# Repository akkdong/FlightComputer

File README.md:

# Flight Computer(Assistant)

## Hardware 
* Raspberry PI Zero
* E-Ink
* STM32H7 Dual core
* Peripherals
  * 10DOF IMU
  * GPS
  * SD-Card
  * Battery change
  * Codec
  * ...
  <p>

  <p>
* ...

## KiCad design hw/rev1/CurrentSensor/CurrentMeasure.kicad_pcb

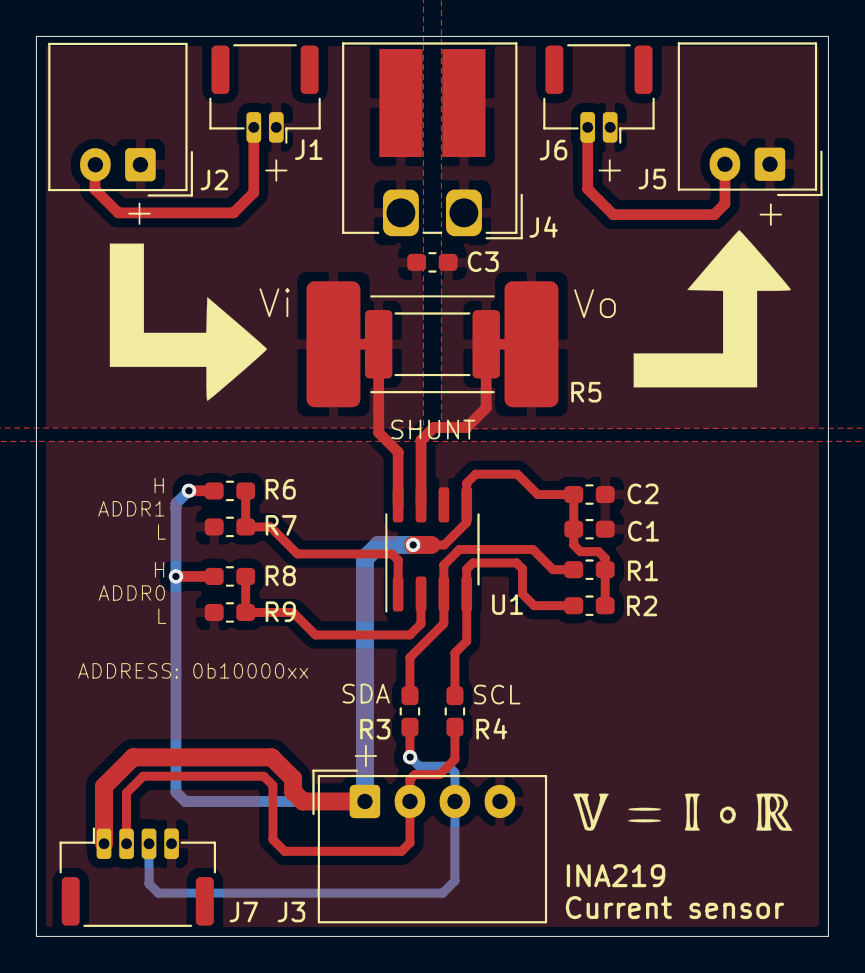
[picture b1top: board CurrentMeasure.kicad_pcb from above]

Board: 2 copper layers, 44.0 x 50.0 mm, 21 parts (0 on the bottom side), 10 nets.

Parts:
C1, C3: 0.1uF; C_0603_1608Metric_Pad1.05x0.95mm_HandSolder
C2: 10Uf; C_0603_1608Metric_Pad1.05x0.95mm_HandSolder
J1, J6: Conn_01x02; Molex_CLIK-Mate_502386-0270_1x02-1MP_P1.25mm_Horizontal
J2, J5: Conn_01x02; Molex_SPOX_5268-02A_1x02_P2.50mm_Horizontal
J3: Conn_01x04; Molex_SPOX_5268-04A_1x04_P2.50mm_Horizontal
J4: Conn_01x02; Wago_734-162_1x02_P3.50mm_Horizontal
J7: Conn_01x04; Molex_CLIK-Mate_502386-0470_1x04-1MP_P1.25mm_Horizontal
R1, R2: 10K; R_0603_1608Metric_Pad1.05x0.95mm_HandSolder
R3, R4: 33R; R_0603_1608Metric_Pad1.05x0.95mm_HandSolder
R5: 2mR; R_2512_6332Metric_Pad1.52x3.35mm_HandSolder
R6, R7, R8, R9: 100R; R_0603_1608Metric_Pad1.05x0.95mm_HandSolder
R10: N/C; R_4527
U1: INA219AxD; SOIC-8_3.9x4.9mm_P1.27mm

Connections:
/VIN: C3.1, J1.1, J2.1, J4.2, R5.1, R10.1, U1.8
/VOUT: C3.2, J4.1, J5.1, J6.1, R5.2, R10.2, U1.7
GND: C1.2, C2.2, J1.2, J2.2, J3.4, J5.2, J6.2, J7.4, R7.2, R9.2, U1.6
unnamed: J3.2, J7.2, R4.1
unnamed: J3.3, J7.3, R3.1
unnamed: R1.2, R3.2, U1.3
unnamed: R2.2, R4.2, U1.4
unnamed: R6.1, R7.1, U1.1
unnamed: R8.1, R9.1, U1.2
VCC: C1.1, C2.1, J3.1, J7.1, R1.1, R2.1, R6.2, R8.2, U1.5

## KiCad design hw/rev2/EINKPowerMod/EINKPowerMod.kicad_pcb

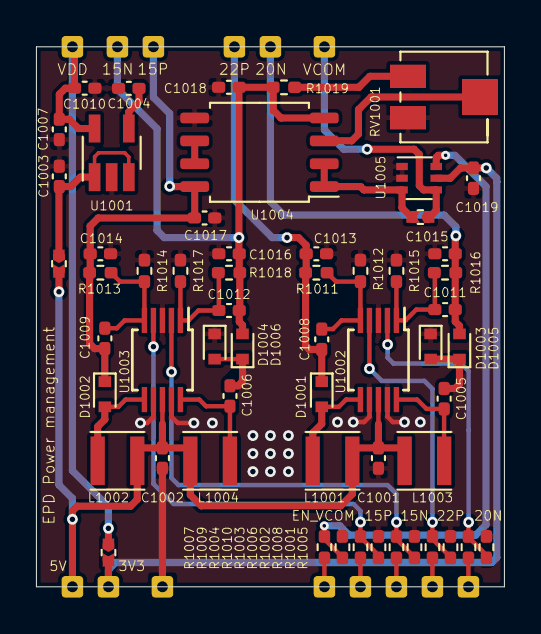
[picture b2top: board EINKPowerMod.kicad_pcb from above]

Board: 2 copper layers, 26.0 x 30.0 mm, 71 parts (0 on the bottom side), 35 nets.

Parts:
C1001, C1002: 4.7uF; C_0402_1005Metric_Pad0.74x0.62mm_HandSolder
C1003, C1004, C1013, C1014, C1015, C1016: 1uF; C_0402_1005Metric_Pad0.74x0.62mm_HandSolder
C1005, C1006, C1007, C1017, C1018, C1019: 0.1uF; C_0402_1005Metric_Pad0.74x0.62mm_HandSolder
C1008, C1009: 4.7pF; C_0402_1005Metric_Pad0.74x0.62mm_HandSolder
C1010: 10uF; C_0402_1005Metric_Pad0.74x0.62mm_HandSolder
C1011, C1012: 100pF; C_0402_1005Metric_Pad0.74x0.62mm_HandSolder
D1001, D1002, D1003, D1004, D1005, D1006: 1N4001; D_SOD-523
J1001, J1002, J1003, J1004, J1005, J1006, J1007, J1008, J1009, J1010, J1011, J1012, J1013, J1014: Conn_01x01; PMIC_HOLE
JP1001: Close; Jumper_0402_1005Metric
JP1002, JP1003: Open; Jumper_0402_1005Metric
L1001, L1002, L1003, L1004: 22uH; L_Taiyo-Yuden_MD-3030
R1001, R1002, R1003, R1004, R1007: 33R; R_0402_1005Metric_Pad0.72x0.64mm_HandSolder
R1005, R1006, R1008, R1009, R1010: 100K; R_0402_1005Metric_Pad0.72x0.64mm_HandSolder
R1011: 2M; R_0402_1005Metric_Pad0.72x0.64mm_HandSolder
R1012: 120K; R_0402_1005Metric_Pad0.72x0.64mm_HandSolder
R1013: 300K; R_0402_1005Metric_Pad0.72x0.64mm_HandSolder
R1014: 27K; R_0402_1005Metric_Pad0.72x0.64mm_HandSolder
R1015: 39K; R_0402_1005Metric_Pad0.72x0.64mm_HandSolder
R1016: 560K; R_0402_1005Metric_Pad0.72x0.64mm_HandSolder
R1017: 10K; R_0402_1005Metric_Pad0.72x0.64mm_HandSolder
R1018: 110K; R_0402_1005Metric_Pad0.72x0.64mm_HandSolder
R1019: 200K; R_0402_1005Metric_Pad0.72x0.64mm_HandSolder
RV1001: 100K; Potentiometer_Bourns_3214J_Horizontal
U1001: XC6220B331MR-G; SOT-23-5_HandSoldering
U1002, U1003: LT1945; MSOP-10_3x3mm_P0.5mm
U1004: LM358; SOIC-8_5.275x5.275mm_P1.27mm
U1005: NC7SB3157P6X; SOT-363_SC-70-6

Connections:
+15V: C1009.1, C1014.1, C1017.1, D1002.1, J1012.1, R1013.2, U1004.8
+22V: C1008.1, C1013.1, D1001.1, J1009.1, R1011.2
-15V: C1012.2, C1016.1, C1018.2, D1006.2, J1013.1, R1018.2, R1019.2, U1004.4
-20V: C1011.2, C1015.1, D1005.2, J1010.1, R1016.2
/EN_15N: J1005.1, R1003.2
/EN_15P: J1004.1, R1004.2
/EN_20N: J1007.1, R1001.2
/EN_22P: J1006.1, R1002.2
/EN_VCOM: J1008.1, R1007.1
GND: C1001.2, C1002.2, C1003.1, C1004.1, C1007.1, C1010.2, C1013.2, C1014.2, C1015.2, C1016.2, C1017.2, C1018.1, C1019.1, D1003.1, D1004.1, J1003.1, R1005.2, R1006.2, R1008.2, R1009.2, R1010.2, R1012.2, R1014.2, R1015.2, R1017.2, RV1001.1, U1001.2, U1002.3, U1002.7, U1002.9, U1003.3, U1003.7, U1003.9, U1004.5, U1005.1, U1005.2
unnamed: C1003.2, JP1001.2, U1001.1, U1001.3
unnamed: C1004.2, U1001.4
unnamed: C1005.1, D1003.2, D1005.1
unnamed: C1005.2, L1003.1, U1002.10
unnamed: C1006.1, D1004.2, D1006.1
unnamed: C1006.2, L1004.1, U1003.10
unnamed: C1008.2, R1011.1, R1012.1, U1002.5
unnamed: C1009.2, R1013.1, R1014.1, U1003.5
unnamed: C1011.1, R1015.1, R1016.1, U1002.1
unnamed: C1012.1, R1017.1, R1018.1, U1003.1
unnamed: D1001.2, L1001.2, U1002.6
unnamed: D1002.2, L1002.2, U1003.6
unnamed: JP1003.1, U1004.1, U1004.2, U1005.3
unnamed: R1001.1, R1005.1, U1002.2
unnamed: R1002.1, R1008.1, U1002.4
unnamed: R1003.1, R1006.1, U1003.2
unnamed: R1004.1, R1010.1, U1003.4
unnamed: R1007.2, R1009.1, U1005.6
unnamed: R1019.1, RV1001.3
unnamed: RV1001.2, U1004.3
unnamed: U1004.6, U1004.7
VCC_3V3: C1019.2, J1002.1, JP1002.1, U1005.5
VCC_5V: C1001.1, C1002.1, J1001.1, JP1001.1, L1001.1, L1002.1, L1003.2, L1004.2, U1002.8, U1003.8
VCC_EINK: C1007.2, C1010.1, J1014.1, JP1002.2, U1001.5
VCOM: J1011.1, JP1003.2, U1005.4

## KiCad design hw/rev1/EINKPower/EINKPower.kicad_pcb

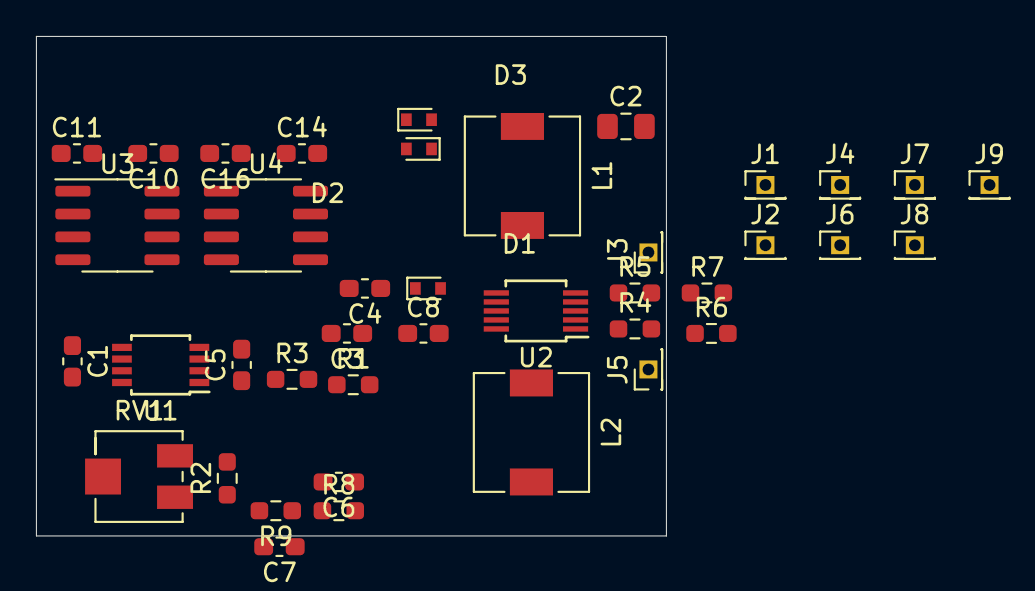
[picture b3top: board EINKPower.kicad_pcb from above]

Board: 2 copper layers, 35.0 x 27.8 mm, 40 parts (0 on the bottom side), 18 nets, no tracks yet.

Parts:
C1, C5, C8: 0.1uF; C_0603_1608Metric_Pad1.05x0.95mm_HandSolder
C2: 4.7uF; C_0805_2012Metric_Pad1.15x1.40mm_HandSolder
C3: 4.7pF; C_0603_1608Metric_Pad1.05x0.95mm_HandSolder
C4, C6, C11, C16: 1uF; C_0603_1608Metric_Pad1.05x0.95mm_HandSolder
C7: 100pF; C_0603_1608Metric_Pad1.05x0.95mm_HandSolder
C10, C14: 4.7uF; C_0603_1608Metric_Pad1.05x0.95mm_HandSolder
D1, D2, D3: 1N4001; D_SOD-523
J1, J2, J3, J4, J5, J6, J7, J8, J9: Conn_01x01; PinHeader_1x01_P1.27mm_Vertical
L1, L2: 22uH; L_6.3x6.3_H3
R1: 2M; R_0603_1608Metric_Pad0.98x0.95mm_HandSolder
R2: 200K; R_0603_1608Metric_Pad0.98x0.95mm_HandSolder
R3: 120K; R_0603_1608Metric_Pad0.98x0.95mm_HandSolder
R4, R5: 33R; R_0603_1608Metric_Pad0.98x0.95mm_HandSolder
R6, R7: 100K; R_0603_1608Metric_Pad0.98x0.95mm_HandSolder
R8: 39K; R_0603_1608Metric_Pad0.98x0.95mm_HandSolder
R9: 560K; R_0603_1608Metric_Pad0.98x0.95mm_HandSolder
RV1: 100K; Potentiometer_Bourns_3214J_Horizontal
U1: LM358; TSSOP-8_3x3mm_P0.65mm
U2: LT1945; MSOP-10_3x3mm_P0.5mm
U3: MC78L15_SO8; SOIC-8_3.9x4.9mm_P1.27mm
U4: MC79L15_SO8; SOIC-8_3.9x4.9mm_P1.27mm

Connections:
+15V: C1.1, C11.1, J8.1, U1.8, U3.1
+22V: C3.1, C4.1, C10.1, D1.1, J1.1, R1.2, U3.8
-15V: C5.2, C16.2, J9.1, R2.2, U1.4, U4.1
-20V: C6.1, C7.2, C14.2, D3.2, J4.1, R9.2, U4.2, U4.3, U4.6, U4.7
/EN_VDD: J3.1, R5.2
/EN_VEE: J5.1, R4.2
GND: C1.2, C2.2, C4.2, C5.1, C6.2, C10.2, C11.2, C14.1, C16.1, D2.1, J6.1, R3.2, R6.2, R7.2, R8.2, RV1.1, U2.3, U2.7, U2.9, U3.2, U3.3, U3.6, U3.7, U4.5
unnamed: C3.2, R1.1, R3.1, U2.5
unnamed: C7.1, R8.1, R9.1, U2.1
unnamed: C8.1, D2.2, D3.1
unnamed: C8.2, L2.1, U2.10
unnamed: D1.2, L1.2, U2.6
unnamed: R2.1, RV1.3
unnamed: R4.1, R6.1, U2.2
unnamed: R5.1, R7.1, U2.4
unnamed: RV1.2, U1.3
VCC_5V: C2.1, J2.1, L1.1, L2.2, U2.8
VCOM: J7.1, U1.1, U1.2

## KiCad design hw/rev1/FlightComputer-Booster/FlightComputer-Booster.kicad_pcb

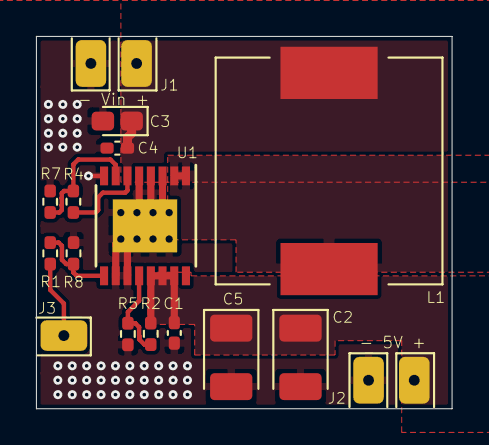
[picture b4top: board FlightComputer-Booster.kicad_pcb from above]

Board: 2 copper layers, 23.1 x 20.7 mm, 16 parts (0 on the bottom side), 8 nets.

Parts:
C1: 2.2uF; C_0402_1005Metric_Pad0.74x0.62mm_HandSolder
C2, C5: 100uF; CP_EIA-3528-15_AVX-H_Pad1.50x2.35mm_HandSolder
C3: 10uF; CP_EIA-1608-08_AVX-J_Pad1.25x1.05mm_HandSolder
C4: 0.1uF; C_0402_1005Metric_Pad0.74x0.62mm_HandSolder
J1, J2: Conn_01x02; PinHeader_1x02_P2.54mm_Vertical
J3: Conn_01x01; PinHeader_1x01_P2.54mm_Vertical
L1: 68uH w/2A; L_12x12mm_H6mm
R1: 33R; R_0402_1005Metric_Pad0.72x0.64mm_HandSolder
R2, R4: 1.87M; R_0402_1005Metric_Pad0.72x0.64mm_HandSolder
R5, R7: 340K; R_0402_1005Metric_Pad0.72x0.64mm_HandSolder
R8: 100K; R_0402_1005Metric_Pad0.72x0.64mm_HandSolder
U1: TPS61032PWR; TSSOP-16-1EP_4.4x5mm_P0.65mm

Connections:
/EN: R1.2, R8.1, U1.9
/FB: R2.2, R5.1, U1.12
/LBI: R4.2, R7.1, U1.7
/SW: L1.2, U1.1, U1.2
GND: C1.2, C2.2, C3.2, C4.2, C5.2, J1.2, J2.2, R5.2, R7.2, R8.2, U1.3, U1.4, U1.5, U1.8, U1.10, U1.11, U1.17
unnamed: J3.1, R1.1
VCC_5V: C1.1, C2.1, C5.1, J2.1, R2.1, U1.13, U1.14, U1.15
VCC_BAT: C3.1, C4.1, J1.1, L1.1, R4.1, U1.6

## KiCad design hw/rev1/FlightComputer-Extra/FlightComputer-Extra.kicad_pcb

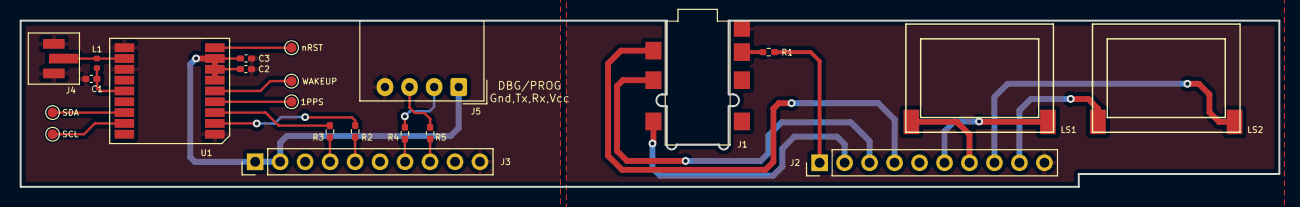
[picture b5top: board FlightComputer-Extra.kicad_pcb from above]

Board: 2 copper layers, 128.0 x 16.9 mm, 22 parts (0 on the bottom side), 27 nets.

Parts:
C1: 22pF; C_0402_1005Metric_Pad0.74x0.62mm_HandSolder
C2: 0.1uF; C_0402_1005Metric_Pad0.74x0.62mm_HandSolder
C3: 1uF; C_0402_1005Metric_Pad0.74x0.62mm_HandSolder
J1: SJ-43617-SMT
J2, J3: Conn_01x10; PinHeader_1x10_P2.54mm_Vertical
J4: IPEX_IPX; IPEX-IPX
J5: Conn_DEBUG; Molex_SPOX_5268-04A_1x04_P2.50mm_Horizontal
L1: 33nH; L_0402_1005Metric
LS1, LS2: Speaker; SM150808-8
R1: 100K; R_0402_1005Metric_Pad0.72x0.64mm_HandSolder
R2, R3, R4, R5: 33R; R_0402_1005Metric_Pad0.72x0.64mm_HandSolder
TP1: SCL; TestPoint_Pad_D1.0mm
TP2: SDA; TestPoint_Pad_D1.0mm
TP3: nRST; TestPoint_Pad_D1.0mm
TP4: WAKEUP; TestPoint_Pad_D1.0mm
TP5: 1PPS; TestPoint_Pad_D1.0mm
U1: Teseo-LIV3F

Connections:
/DEBUG_RX: J3.7, R4.2
/DEBUG_TX: J3.8, R5.2
/GPS_RX: J3.4, R3.1
/GPS_TX: J3.5, R2.1
/HP_DETECT: J1.4, J2.4
/HP_LEFT: J1.2, J2.2
/HP_RIGHT: J1.3, J2.3
/SPK_LN: J2.7, LS1.2
/SPK_LP: J2.6, LS1.1
/SPK_RN: J2.9, LS2.2
/SPK_RP: J2.8, LS2.1
GND: C1.1, C2.1, C3.1, J3.10, J4.2, J4.3, J5.4, U1.1, U1.10, U1.12
GNDA: J1.1, J2.10
unnamed: C1.2, L1.1, U1.14
unnamed: J1.12, R1.2
unnamed: J4.1, L1.2, U1.11
unnamed: J5.2, R4.1
unnamed: J5.3, R5.1
unnamed: R2.2, U1.2
unnamed: R3.2, U1.3
unnamed: TP1.1, U1.17
unnamed: TP2.1, U1.16
unnamed: TP3.1, U1.9
unnamed: TP4.1, U1.5
unnamed: TP5.1, U1.4
VCC_3V3: J2.1, R1.1
VCC_PERIH: C2.2, C3.2, J3.1, J3.2, J5.1, U1.6, U1.7, U1.8

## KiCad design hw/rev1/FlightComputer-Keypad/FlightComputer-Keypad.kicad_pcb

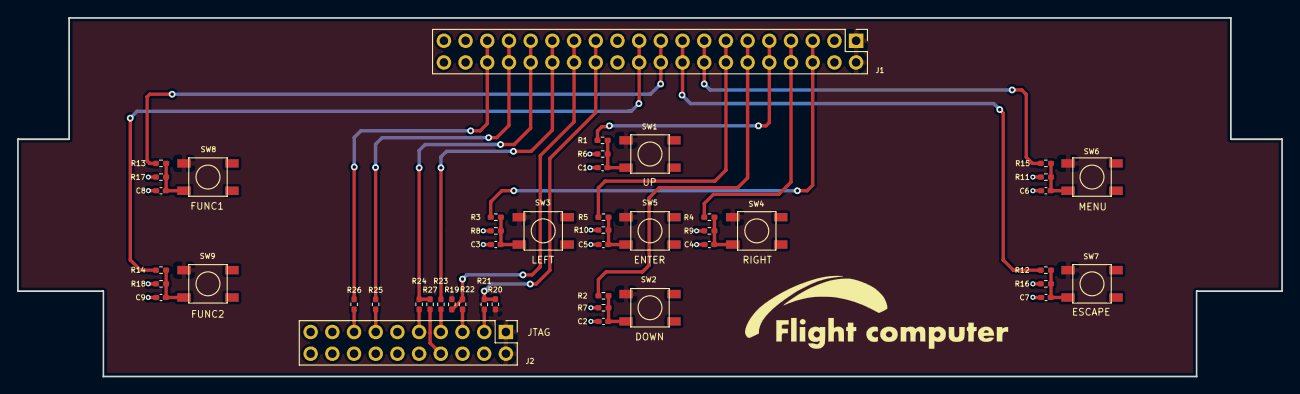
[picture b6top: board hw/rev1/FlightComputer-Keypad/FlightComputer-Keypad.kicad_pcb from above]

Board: 2 copper layers, 148.0 x 42.0 mm, 47 parts (0 on the bottom side), 32 nets.

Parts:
C1, C2, C3, C4, C5, C6, C7, C8, C9: 0.1uF; C_0402_1005Metric_Pad0.74x0.62mm_HandSolder
J1: Conn_02x20_Odd_Even; PinHeader_2x20_P2.54mm_Vertical
J2: Conn_02x10_Odd_Even; PinHeader_2x10_P2.54mm_Vertical
R1, R2, R3, R4, R5, R11, R12, R13, R14: 1K; R_0402_1005Metric_Pad0.72x0.64mm_HandSolder
R6, R7, R8, R9, R10, R15, R16, R17, R18, R19, R20, R27: 100K; R_0402_1005Metric_Pad0.72x0.64mm_HandSolder
R21, R22, R23, R24, R25, R26: 33R; R_0402_1005Metric_Pad0.72x0.64mm_HandSolder
SW1, SW2, SW3, SW4, SW5, SW6, SW7, SW8, SW9: SW_Push; SW-SPST-PTS647

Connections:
/KEY_DOWN: J1.11, J1.12, R2.2
/KEY_ENTER: J1.13, J1.14, R5.2
/KEY_ESCAPE: J1.17, J1.18, R12.2
/KEY_FUNC1: J1.19, J1.20, R13.2
/KEY_FUNC2: J1.21, J1.22, R14.2
/KEY_LEFT: J1.5, J1.6, R3.2
/KEY_MENU: J1.15, J1.16, R11.2
/KEY_RIGHT: J1.7, J1.8, R4.2
/KEY_UP: J1.9, J1.10, R1.2
/TCLK: J1.31, J1.32, R24.1, R27.1
/TDI: J1.27, J1.28, R19.2, R22.1
/TDO: J1.33, J1.34, R25.1
/TMS: J1.29, J1.30, R23.1
/TRST: J1.25, J1.26, R20.2, R21.1
/nRESET: J1.35, J1.36, R26.1
GND: C1.2, C2.2, C3.2, C4.2, C5.2, C6.2, C7.2, C8.2, C9.2, J1.39, J1.40, J2.4, J2.6, J2.8, J2.10, J2.12, J2.14, J2.16, J2.18, J2.20, R6.1, R7.1, R8.1, R9.1, R10.1, R15.1, R16.1, R17.1, R18.1, R27.2
unnamed: C1.1, R1.1, R6.2, SW1.1
unnamed: C2.1, R2.1, R7.2, SW2.1
unnamed: C3.1, R3.1, R8.2, SW3.1
unnamed: C4.1, R4.1, R9.2, SW4.1
unnamed: C5.1, R5.1, R10.2, SW5.1
unnamed: C6.1, R11.1, R15.2, SW6.1
unnamed: C7.1, R12.1, R16.2, SW7.1
unnamed: C8.1, R13.1, R17.2, SW8.1
unnamed: C9.1, R14.1, R18.2, SW9.1
unnamed: J2.3, R21.2
unnamed: J2.5, R22.2
unnamed: J2.7, R23.2
unnamed: J2.9, R24.2
unnamed: J2.13, R25.2
unnamed: J2.15, R26.2
VCC_MCU: J1.1, J1.2, J2.1, J2.2, R19.1, R20.1, SW1.2, SW2.2, SW3.2, SW4.2, SW5.2, SW6.2, SW7.2, SW8.2, SW9.2

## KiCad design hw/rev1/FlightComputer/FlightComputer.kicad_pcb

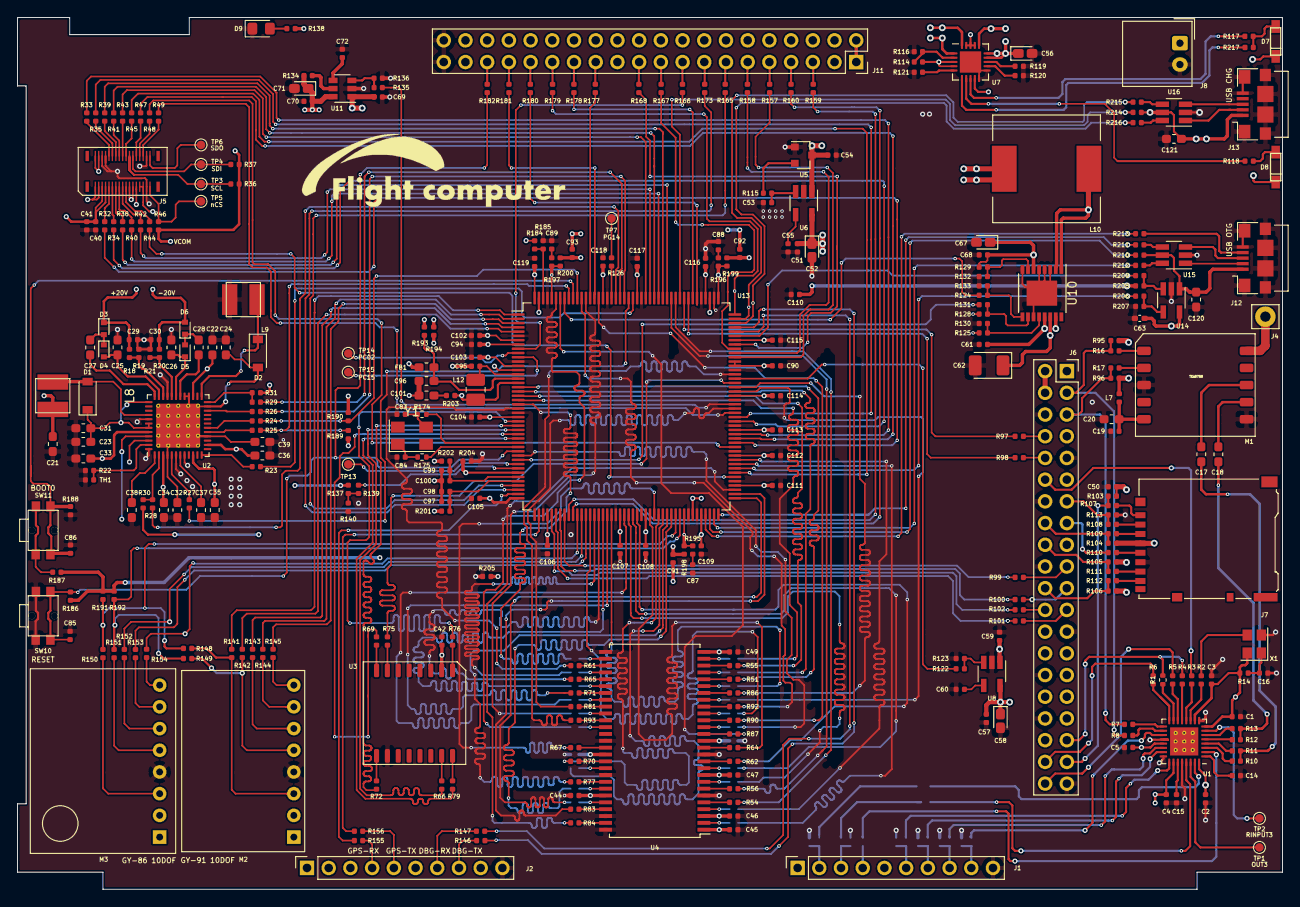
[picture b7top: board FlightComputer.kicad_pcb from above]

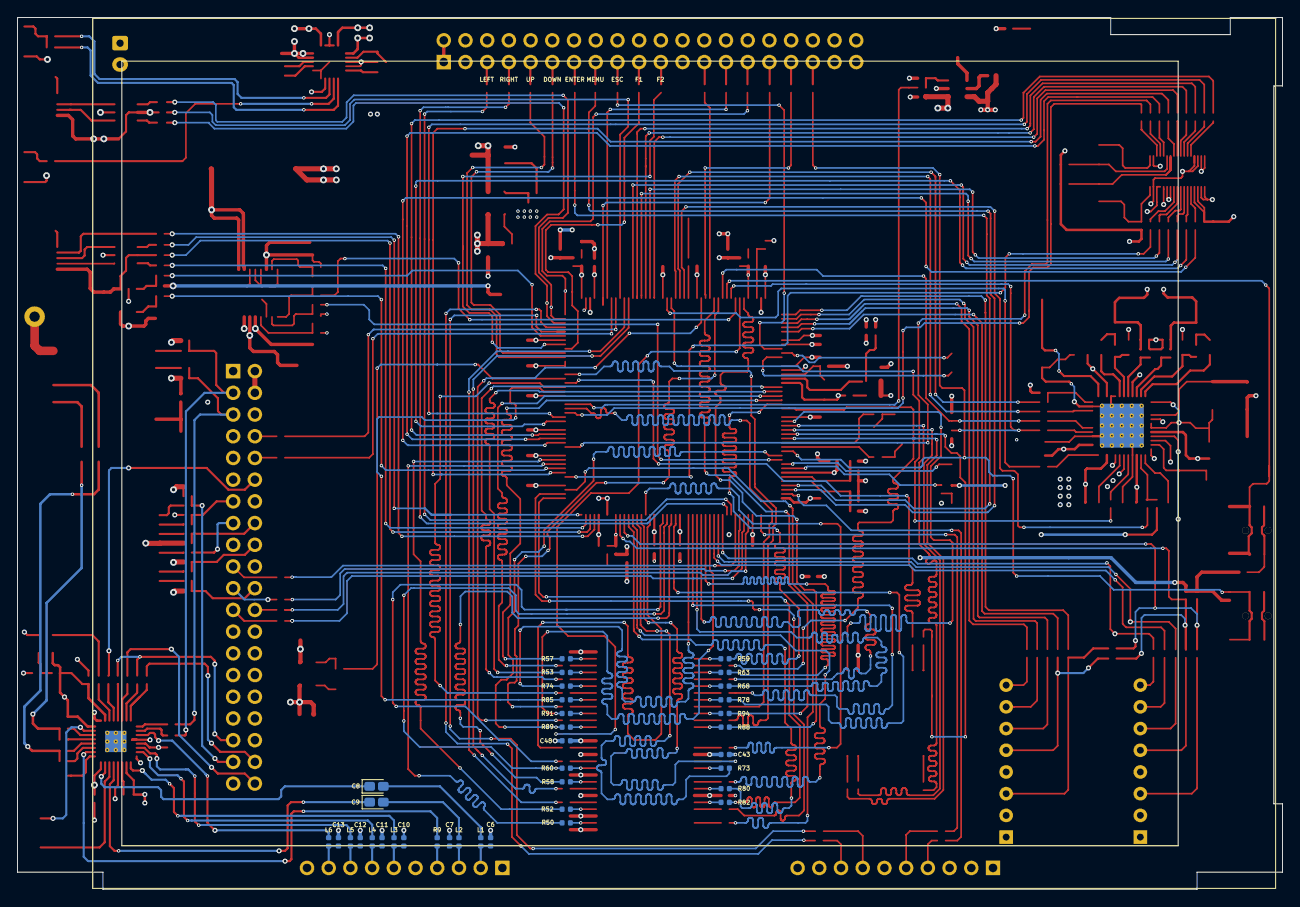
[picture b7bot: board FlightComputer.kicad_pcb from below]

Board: 4 copper layers, 148.0 x 102.0 mm, 376 parts (36 on the bottom side), 373 nets.

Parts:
C1, C2, C3, C16, C19, C41, C42, C43, C44, C45, C46, C47, C48, C49, C50, C51, C57, C68, C70, C85, C86, C87, C88, C89, C94, C98, C100, C102, C103, C104, C105, C106, C107, C108, C109, C111, C112, C113, C114, C115, C116, C117, C118, C119: 0.1uF; C_0402_1005Metric
C4, C5, C14, C15, C91, C92, C93, C110: 4.7uF; C_0402_1005Metric
C6, C7, C10, C11, C12, C13, C95: 220pF; C_0402_1005Metric
C8, C9, C52, C56, C58, C67, C71: 10uF; CP_EIA-1608-08_AVX-J_Pad1.25x1.05mm_HandSolder
C17, C18, C20, C21, C22, C35, C96, C101, C120, C121: 10uF; C_0603_1608Metric_Pad1.05x0.95mm_HandSolder
C23, C24, C31, C32, C33, C34, C36, C37, C38, C39: 4.7uF; C_0603_1608Metric_Pad1.05x0.95mm_HandSolder
C25, C26: 0.1uF; C_0603_1608Metric_Pad1.05x0.95mm_HandSolder
C27, C28: 0.01uF; C_0603_1608Metric_Pad1.05x0.95mm_HandSolder
C29, C30, C61: 2.2uF; C_0402_1005Metric
C40, C53, C54, C59, C69, C90, C97, C99: 1uF; C_0402_1005Metric
C55, C60, C72: N/C; C_0402_1005Metric
C62: 100uF; CP_EIA-3528-15_AVX-H_Pad1.50x2.35mm_HandSolder
C63: 2.2uF; C_0402_1005Metric_Pad0.74x0.62mm_HandSolder
C83, C84: 18pF; C_0402_1005Metric
D1, D2: MBR130T1G; D_SOD-123
D3, D4, D5: RB531SM; D_SOD-523
D6: BAT54-SOT23; D_SOD-523
D7: LED_R; SML-LXR85GC-TR
D8: LED_G; SML-LXR85GC-TR
D9: LED_G; D_0805_2012Metric_Pad1.15x1.40mm_HandSolder
FB1: BEAD(BMJ1608HM180NTR); L_0603_1608Metric_Pad1.05x0.95mm_HandSolder
J1, J2: Conn_01x10; PinSocket_1x10_P2.54mm_Vertical
J4: Conn_01x01; Pin_D1.2mm_L10.2mm_W2.9mm_FlatFork
J5: ED060SC7_EPD; AXT334124
J6: RPI_Connector; PinSocket_2x20_P2.54mm_Vertical
J7: Micro_SD_Card; microSD_HC_Hirose_DM3AT-SF-PEJM5
J8: Conn_01x02; Molex_SPOX_5268-02A_1x02_P2.50mm_Horizontal
J11: Conn_02x20_Odd_Even; PinSocket_2x20_P2.54mm_Vertical
J12, J13: USB_B_Micro; USB_Micro-B_TE-1981568-1
L1, L2, L3, L4, L5, L6, L7: Ferrite; L_0402_1005Metric
L8: 2.2uH; L_1515(4040 metric)
L9: 4.7uH; L_1515(4040 metric)
L10: 68uH w/2A; L_12x12mm_H6mm
L12: 2.2uH (LQM2MPN2R2NG0); L_1008_2520Metric_Pad1.43x2.20mm_HandSolder
M1: TEA5767_Radio_Module; TEA5756-TJ-102BC
M2: GY-91
M3: GY-86
R1, R2, R3, R4, R5, R6, R7, R8, R9, R10, R13, R16, R17, R23, R24, R25, R26, R27, R28, R29, R32, R33, R34, R35, R38, R39, R40, R41, R42, R43, R44, R45, R47, R48, R49, R50, R51, R52, R53, R54, R55, R56, R57, R58, R59, R60, R61, R62, R63, R64, R65, R66, R67, R68, R69, R70, R71, R72, R73, R74, R75, R76, R77, R78, R79, R80, R81, R82, R83, R84, R85, R86, R87, R88, R89, R90, R91, R92, R93, R94, R97, R98, R99, R100, R101, R102, R107, R108, R109, R110, R111, R112, R122, R124, R131, R135, R141, R142, R143, R144, R145, R146, R147, R150, R151, R152, R153, R154, R155, R156, R177, R178, R179, R180, R181, R182, R206, R209, R210, R211, R212, R213, R214, R215, R216: 33R; R_0402_1005Metric
R11, R12, R117, R126, R148, R149, R185, R193, R195, R196, R197, R200: N/C; R_0402_1005Metric
R14, R30, R31, R36, R37, R46, R184, R189, R190, R191, R192, R207: 10K; R_0402_1005Metric
R18, R20, R115, R128, R140: 1M; R_0402_1005Metric
R19: 47.5K; R_0402_1005Metric
R21: 52.3K; R_0402_1005Metric
R22: 43K; R_0402_1005Metric
R95, R96, R103, R104, R105, R106: 47K; R_0402_1005Metric
R113, R116, R120, R123, R133, R136, R186, R188: 100K; R_0402_1005Metric
R114: 270K; R_0402_1005Metric
R118, R119, R134, R138, R187, R217: 1K; R_0402_1005Metric
R121: 15K; R_0402_1005Metric
R125, R129: 1.87M; R_0402_1005Metric
R130, R132: 340K; R_0402_1005Metric
R137: 560K; R_0402_1005Metric
R139, R157, R158, R159, R160, R165, R166, R167, R168, R173, R174, R175, R194, R198, R199, R201, R202, R203, R204, R205: 0R; R_0402_1005Metric
R208: 47k; R_0402_1005Metric
SW10, SW11: SW_Push; SW-TACT-436351045816
TH1: NCP18XH103F03RB(10K); R_0402_1005Metric
TP1: OUT3; TestPoint_Pad_D1.0mm
TP2: RINPUT3; TestPoint_Pad_D1.0mm
TP3: EINK_SPI_SCL; TestPoint_Pad_D1.0mm
TP4: EINK_SPI_SDI; TestPoint_Pad_D1.0mm
TP5: EINK_SPI_CS; TestPoint_Pad_D1.0mm
TP6: EINK_SPI_SDO; TestPoint_Pad_D1.0mm
TP7: TP_EXTRA_PWR; TestPoint_Pad_D1.0mm
TP13: PC2; TestPoint_Pad_D1.0mm
TP14: PC14; TestPoint_Pad_D1.0mm
TP15: PC15; TestPoint_Pad_D1.0mm
U1: WM8960; QFN-32-1EP_5x5mm_P0.5mm_EP3.3x3.3mm_ThermalVias
U2: TPS65186; VQFN-48-1EP_7x7mm_P0.5mm_EP5.15x5.15mm_ThermalVias
U3: MT25QL512ABB8ESF; SOP2-16_7.5x10.3mm_P1.27mm
U4: MT48LC16M16A2P; TSOP-II-54_22.2x10.16mm_P0.8mm
U5: MAX809TTRG; SOT-23
U6, U8: XC6220B331MR-G; SOT-23-5_HandSoldering
U7: MCP73871; QFN-20-1EP_4x4mm_P0.5mm_EP2.5x2.5mm
U10: TPS61032PWR; TSSOP-16-1EP_4.4x5mm_P0.65mm
U11: TPS22917DBV; SOT-23-6
U13: STM32H745IIT; LQFP-176_24x24mm_P0.5mm
U14: STMPS2151STR; SOT-23-5_HandSoldering
U15, U16: USBLC6-2SC6; SOT-23-6_Handsoldering
X1: 24MHz; Oscillator_SMD_Abracon_ASE-4Pin_3.2x2.5mm
Y1: 25MHz; Crystal_SMD_5032-4Pin_5.0x3.2mm

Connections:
+15V: C33.1, J5.2, J5.4, U2.44
+22V: C29.2, D3.1, J5.25, R18.1
+BATT: C56.1, J8.1, U7.14, U7.15, U7.16
-15V: C34.2, J5.1, J5.3, U2.3
-20V: C30.1, D6.2, J5.27, J5.29, R20.2
/Codec/HPDETECT: J1.4, R9.2
/Codec/I2C_SCL: J6.5, R7.2, R17.2, R96.2
/Codec/I2C_SDA: J6.3, R8.2, R16.2, R95.2
/Codec/I2S_DIN: J6.40, R5.2
/Codec/I2S_LRCK: J6.35, R1.2, R4.2
/Codec/I2S_MCLK: R2.2, X1.3
/Codec/I2S_SCLK: J6.12, R3.2
/Codec/RADIO_L: C17.2, R10.2, R11.2
/Codec/RADIO_R: C18.2, R12.2, R13.2
/DEBUG/DEBUG_JMS-SWDIO: R179.1, U13.132
/DEBUG/DEBUG_JTCK-SWCLK: R180.1, U13.138
/DEBUG/DEBUG_JTDI: R178.1, U13.139
/DEBUG/DEBUG_JTDO-SWO: R181.1, U13.162
/DEBUG/DEBUG_nJTRST: R177.1, U13.163
/DEBUG/nRST: C85.1, R182.1, R186.1, SW10.1, U13.33
/EINK-PMIC/EPD_CKV: R48.2, U13.101
/EINK-PMIC/EPD_CL: R32.1, U13.102
/EINK-PMIC/EPD_D0: R38.1, U13.145
/EINK-PMIC/EPD_D1: R39.2, U13.146
/EINK-PMIC/EPD_D2: R40.1, U13.147
/EINK-PMIC/EPD_D3: R41.2, U13.148
/EINK-PMIC/EPD_D4: R42.1, U13.149
/EINK-PMIC/EPD_D5: R43.2, U13.150
/EINK-PMIC/EPD_D6: R44.1, U13.94
/EINK-PMIC/EPD_D7: R45.2, U13.95
/EINK-PMIC/EPD_GMODE: R47.2, U13.103
/EINK-PMIC/EPD_LE: R33.2, U13.104
/EINK-PMIC/EPD_OE: R34.1, U13.107
/EINK-PMIC/EPD_PMIC_PWRUP: R26.1, U13.155
/EINK-PMIC/EPD_PMIC_PWR_GOOD: R29.2, U13.156
/EINK-PMIC/EPD_PMIC_SCL: R25.1, R189.2, U13.168
/EINK-PMIC/EPD_PMIC_SDA: R24.1, R190.2, U13.166
/EINK-PMIC/EPD_PMIC_VCOM: R23.1, U13.153
/EINK-PMIC/EPD_PMIC_WAKEUP: R27.1, U13.154
/EINK-PMIC/EPD_PMIC_nINT: R28.2, U13.157
/EINK-PMIC/EPD_SPH: R35.2, U13.108
/EINK-PMIC/EPD_SPV: R49.2, U13.109
/EINK-PMIC/VCOM: C36.1, J5.21, J5.23, U2.14
/EINK_MISO: R100.2, U13.51
/EINK_MOSI: R99.2, U13.52
/EINK_SCLK: R101.2, U13.50
/EINK_nCS: R102.1, U13.49
/IMU1_MISO: R143.2, U13.4
/IMU1_MOSI: R142.2, U13.5
/IMU1_SCLK: R141.2, U13.1
/IMU1_nCS1: R144.2, U13.2
/IMU1_nCS2: R145.2, U13.3
/IMU2_DRDY: R154.2, U13.55
/IMU2_FSYNC: R152.2, U13.56
/IMU2_SCL: R148.1, R150.2, R191.2, U13.78
/IMU2_SDA: R149.1, R151.2, R192.2, U13.79
/IMU2_nINT: R153.2, U13.57
/KEYBOARD/KEY_DOWN: R158.2, U13.123
/KEYBOARD/KEY_ENTER: R165.2, U13.41
/KEYBOARD/KEY_ESCAPE: R166.2, U13.9
/KEYBOARD/KEY_FUNC1: R167.2, U13.124
/KEYBOARD/KEY_FUNC2: R168.2, U13.125
/KEYBOARD/KEY_LEFT: R159.2, U13.53
/KEYBOARD/KEY_MENU: R173.2, U13.42
/KEYBOARD/KEY_RIGHT: R160.2, U13.54
/KEYBOARD/KEY_UP: R157.2, U13.122
/MCU/BAT_SENSING: R139.1, U13.37
/MCU/BOOT0: C86.1, R188.2, SW11.1, U13.167
/MCU/FMC_A0: R51.2, U13.18
/MCU/FMC_A1: R53.2, U13.19
/MCU/FMC_A2: R55.2, U13.20
/MCU/FMC_A3: R57.2, U13.21
/MCU/FMC_A4: R59.2, U13.22
/MCU/FMC_A5: R61.2, U13.23
/MCU/FMC_A6: R63.2, U13.59
/MCU/FMC_A7: R65.2, U13.60
/MCU/FMC_A8: R68.2, U13.61
/MCU/FMC_A9: R71.2, U13.62
/MCU/FMC_A10: R74.2, U13.63
/MCU/FMC_A11: R78.2, U13.66
/MCU/FMC_A12: R81.2, U13.110
/MCU/FMC_BA0: R85.2, U13.114
/MCU/FMC_BA1: R86.2, U13.115
/MCU/FMC_CKE1: R94.2, U13.164
/MCU/FMC_CLK: R93.2, U13.118
/MCU/FMC_D0: R50.1, U13.97
/MCU/FMC_D1: R52.1, U13.98
/MCU/FMC_D2: R54.1, U13.143
/MCU/FMC_D3: R56.1, U13.144
/MCU/FMC_D4: R58.1, U13.67
/MCU/FMC_D5: R60.1, U13.68
/MCU/FMC_D6: R62.1, U13.69
/MCU/FMC_D7: R64.1, U13.72
/MCU/FMC_D8: R67.1, U13.73
/MCU/FMC_D9: R70.1, U13.74
/MCU/FMC_D10: R73.1, U13.75
/MCU/FMC_D11: R77.1, U13.76
/MCU/FMC_D12: R80.1, U13.77
/MCU/FMC_D13: R82.1, U13.89
/MCU/FMC_D14: R83.1, U13.90
/MCU/FMC_D15: R84.1, U13.91
/MCU/FMC_nBL0: R87.2, U13.170
/MCU/FMC_nBL1: R88.2, U13.171
/MCU/FMC_nCAS: R90.2, U13.161
/MCU/FMC_nE1: R92.2, U13.165
/MCU/FMC_nRAS: R91.2, U13.58
/MCU/FMC_nWE: R89.2, U13.34
/MCU/LOW_BATTERY: R131.2, U13.35
/MCU/MCU_POWER/SMPS_OUT: C91.2, C92.2, C93.2, L12.1, R194.1, R198.1, R199.1, R200.1, R203.2, U13.17
/MCU/MCU_POWER/VCAP: R195.2, R196.2, R197.2, R198.2, R199.2, R200.2, U13.80, U13.133, U13.172
/MCU/MCU_POWER/VDDA: C97.1, C98.1, R201.1, U13.40
/MCU/MCU_POWER/VDDLDO: R193.2, R194.2, U13.82, U13.135, U13.175
/MCU/MCU_POWER/VDDSMPS: C96.1, FB1.2, R193.1, U13.16
/MCU/MCU_POWER/VLXSMPS: C95.1, L12.2, U13.15
/MCU/MCU_POWER/VREF+: C99.1, C100.1, R202.1, U13.39
/MCU/MCU_POWER/VSSA: C97.2, C98.2, C99.2, C100.2, R204.1, U13.38
/MCU/PWR_5V_EN: R124.1, U13.169
/MCU/PWR_BAT+_EN: R135.1, U13.111
/MCU/PWR_EXTRA_EN: R126.1, U13.158
/MCU/PWR_PERIPH_EN: R122.2, U13.117
/MCU/USB_FS_DN: R216.1, U13.130
/MCU/USB_FS_DP: R215.1, U13.131
/MCU/USB_FS_VBUS: R214.1, U13.142
/MCU/USB_HS_DN: R212.1, U13.87
/MCU/USB_HS_DP: R211.1, U13.88
/MCU/USB_HS_ID: R213.1, U13.85
/MCU/USB_HS_OVCR: R209.1, U13.127
/MCU/USB_HS_PWR_EN: R206.1, U13.96
/MCU/USB_HS_VBUS: R210.1, U13.86
/Memory/NOR_CLK: R79.1, U13.30
/Memory/NOR_DQ0: R66.2, U13.28
/Memory/NOR_DQ1: R69.2, U13.29
/Memory/NOR_DQ2: R72.2, U13.27
/Memory/NOR_DQ3: R76.2, U13.26
/Memory/NOR_nCS: R75.1, U13.116
/Raspberry/I2S_DIN: J6.38, R6.2
/Raspberry/SDIO_CLK: J6.15, R110.2
/Raspberry/SDIO_CMD: J6.16, R104.2, R109.2
/Raspberry/SDIO_DAT0: J6.18, R105.2, R111.2
/Raspberry/SDIO_DAT1: J6.22, R106.2, R112.2
/Raspberry/SDIO_DAT2: J6.37, R103.2, R107.2
/Raspberry/SDIO_DAT3: J6.13, R108.2, R113.1
/VARIO_RX: R97.1, U13.141
/VARIO_TX: R98.1, U13.140
/Vario/DEBUG_RX: R147.2, U13.128
/Vario/DEBUG_TX: R146.2, U13.129
/Vario/GPS_RX: R155.2, U13.43
/Vario/GPS_TX: R156.2, U13.46
GND: C1.2, C2.2, C3.2, C4.2, C5.2, C6.2, C7.2, C10.2, C11.2, C12.2, C13.2, C14.2, C15.1, C16.1, C19.2, C20.2, C21.2, C22.1, C23.2, C24.1, C25.2, C26.1, C29.1, C30.2, C31.2, C32.1, C33.2, C34.1, C35.2, C36.2, C37.1, C38.1, C39.1, C40.2, C41.2, C42.2, C43.1, C44.1, C45.1, C46.1, C47.1, C48.1, C49.1, C50.1, C51.2, C52.2, C53.2, C54.2, C55.2, C56.2, C57.2, C58.2, C59.2, C60.2, C61.2, C62.2, C63.2, C67.2, C68.2, C69.2, C70.2, C71.2, C72.2, C83.2, C84.2, C85.2, C86.2, C87.2, C88.2, C89.2, C90.2, C94.2, C102.2, C103.2, C104.2, C105.2, C106.2, C107.2, C108.2, C109.2, C110.2, C111.2, C112.2, C113.2, C114.2, C115.2, C116.2, C117.2, C118.2, C119.2, C120.2, C121.2, D9.1, J1.10, J2.10, J5.6, J5.8, J5.31, J5.32, J6.6, J6.9, J6.14, J6.20, J6.25, J6.30, J6.34, J6.39, J7.6, J8.2, J11.39, J11.40, J12.5, J12.6, J13.5, J13.6, L9.2, M1.3, M1.6, M2.3, M3.3, R19.1, R21.2, R22.1, R113.2, R116.2, R119.2, R120.2, R121.2, R123.1, R130.2, R132.2, R133.2, R136.1, R140.1, R185.1, R188.1, R204.2, R205.2, R207.2, SW10.2, TH1.2, U1.9, U1.20, U1.24, U1.28, U1.33, U2.6, U2.8, U2.33, U2.41, U2.48, U3.10, U4.6, U4.12, U4.28, U4.41, U4.46, U4.52, U4.54, U5.1, U6.2, U7.10, U7.11, U7.21, U8.2, U10.3, U10.4, U10.5, U10.8, U10.11, U10.17, U11.2, U13.6, U13.12, U13.24, U13.45, U13.47, U13.64, U13.70, U13.81, U13.83, U13.93, U13.100, U13.106, U13.112, U13.119, U13.134, U13.137, U13.151, U13.159, U13.173, U14.2, U15.2, U16.2, X1.2
GNDS: C91.1, C92.1, C93.1, C95.2, C96.2, C101.2, R205.1, U13.14
G_KEY_DOWN: J11.11, R158.1
G_KEY_ENTER: J11.13, R165.1
G_KEY_ESCAPE: J11.17, R166.1
G_KEY_FUNC1: J11.19, R167.1
G_KEY_FUNC2: J11.21, R168.1
G_KEY_LEFT: J11.5, R159.1
G_KEY_MENU: J11.15, R173.1
G_KEY_RIGHT: J11.7, R160.1
G_KEY_UP: J11.9, R157.1
unnamed: C6.1, J1.2, L1.2
unnamed: C7.1, J1.3, L2.2
unnamed: C8.1, U1.31
unnamed: C8.2, L1.1
unnamed: C9.1, U1.29
unnamed: C9.2, L2.1
unnamed: C10.1, J1.6, L3.2
unnamed: C11.1, J1.7, L4.2
unnamed: C12.1, J1.8, L5.2
unnamed: C13.1, J1.9, L6.2
unnamed: C14.1, U1.1
unnamed: C15.2, U1.27
unnamed: C16.2, R14.1, X1.1
unnamed: C17.1, M1.8
unnamed: C18.1, M1.7
unnamed: C19.1, C20.1, L7.2, M1.5
unnamed: C23.1, C31.1, D1.1, U2.37, U2.42, U2.43
unnamed: C24.2, C32.2, C39.2, D2.2, U2.4, U2.16, U2.23, U2.28, U2.29, U2.49
unnamed: C25.1, D4.2, U2.35
unnamed: C26.2, D5.1, U2.31
unnamed: C27.1, U2.36
unnamed: C27.2, D3.2, D4.1
unnamed: C28.1, D5.2, D6.1
unnamed: C28.2, U2.30
unnamed: C37.2, U2.7
unnamed: C38.2, U2.1
unnamed: C53.1, R115.1, U6.3
unnamed: C55.1, U6.4
unnamed: C60.1, U8.4
unnamed: C72.1, U11.4
unnamed: C83.1, R174.1, Y1.3
unnamed: C84.1, R175.1, Y1.1
unnamed: C87.1, R195.1
unnamed: C88.1, R196.1
unnamed: C89.1, R197.1
unnamed: C101.1, R203.1
unnamed: C120.1, J12.1, R210.2, U14.1, U15.5
unnamed: D1.2, L8.2, U2.40
unnamed: D2.1, L9.1, U2.25
unnamed: D7.1, R117.1, R217.1
unnamed: D8.1, R118.1
unnamed: D9.2, R138.2
unnamed: J2.4, R155.1
unnamed: J2.5, R156.1
unnamed: J2.7, R147.1
unnamed: J2.8, R146.1
unnamed: J4.1, M1.10
unnamed: J5.9, R32.2
unnamed: J5.10, R33.1
unnamed: J5.11, R34.2
unnamed: J5.12, R35.1
unnamed: J5.13, R38.2
unnamed: J5.14, R39.1
unnamed: J5.15, R40.2
unnamed: J5.16, R41.1
unnamed: J5.17, R42.2
unnamed: J5.18, R43.1
unnamed: J5.19, R44.2
unnamed: J5.20, R45.1
unnamed: J5.22, R36.2, TP3.1
unnamed: J5.24, R37.2, TP4.1
unnamed: J5.26, R47.1
unnamed: J5.28, R48.1
unnamed: J5.30, R49.1
unnamed: J5.33, R46.2, TP5.1
unnamed: J5.34, TP6.1
unnamed: J6.8, R97.2
unnamed: J6.10, R98.2
unnamed: J6.19, R99.1
unnamed: J6.21, R100.1
unnamed: J6.23, R101.1
unnamed: J6.24, R102.2
unnamed: J7.1, R107.1
unnamed: J7.2, R108.1
unnamed: J7.3, R109.1
unnamed: J7.5, R110.1
unnamed: J7.7, R111.1
unnamed: J7.8, R112.1
unnamed: J11.25, R177.2
unnamed: J11.27, R178.2
unnamed: J11.29, R179.2
unnamed: J11.31, R180.2
unnamed: J11.33, R181.2
unnamed: J11.35, R182.2
unnamed: J12.2, U15.1
unnamed: J12.3, U15.3
unnamed: J12.4, R213.2
unnamed: J13.2, U16.1
unnamed: J13.3, U16.3
unnamed: L3.1, U1.25
unnamed: L4.1, U1.23
unnamed: L5.1, U1.22
unnamed: L6.1, U1.19
unnamed: L10.2, U10.1, U10.2
unnamed: M1.1, R16.1
unnamed: M1.2, R17.1
unnamed: M2.4, R141.1, R148.2
unnamed: M2.5, R142.1, R149.2
unnamed: M2.6, R143.1
unnamed: M2.7, R144.1
unnamed: M2.8, R145.1
unnamed: M3.4, R150.1
unnamed: M3.5, R151.1
unnamed: M3.6, R152.1
unnamed: M3.7, R153.1
unnamed: M3.8, R154.1
unnamed: R1.1, U1.15
unnamed: R2.1, U1.11
unnamed: R3.1, U1.12
unnamed: R4.1, U1.13
unnamed: R5.1, U1.14
unnamed: R6.1, U1.16
unnamed: R7.1, U1.17
unnamed: R8.1, U1.18
unnamed: R9.1, U1.2
unnamed: R10.1, U1.3
unnamed: R11.1, U1.4
unnamed: R12.1, U1.5
unnamed: R13.1, U1.6
unnamed: R18.2, R19.2, U2.34
unnamed: R20.1, R21.1, U2.32
unnamed: R22.2, TH1.1, U2.47
unnamed: R23.2, U2.12
unnamed: R24.2, U2.18
unnamed: R25.2, U2.17
unnamed: R26.2, U2.22
unnamed: R27.2, U2.5
unnamed: R28.1, R30.2, U2.2
unnamed: R29.1, R31.2, U2.24
unnamed: R50.2, U4.2
unnamed: R51.1, U4.23
unnamed: R52.2, U4.4
unnamed: R53.1, U4.24
unnamed: R54.2, U4.5
unnamed: R55.1, U4.25
unnamed: R56.2, U4.7
unnamed: R57.1, U4.26
unnamed: R58.2, U4.8
unnamed: R59.1, U4.29
unnamed: R60.2, U4.10
unnamed: R61.1, U4.30
unnamed: R62.2, U4.11
unnamed: R63.1, U4.31
unnamed: R64.2, U4.13
unnamed: R65.1, U4.32
unnamed: R66.1, U3.15
unnamed: R67.2, U4.42
unnamed: R68.1, U4.33
unnamed: R69.1, U3.8
unnamed: R70.2, U4.44
unnamed: R71.1, U4.34
unnamed: R72.1, U3.9
unnamed: R73.2, U4.45
unnamed: R74.1, U4.22
unnamed: R75.2, U3.7
unnamed: R76.1, U3.1
unnamed: R77.2, U4.47
unnamed: R78.1, U4.35
unnamed: R79.2, U3.16
unnamed: R80.2, U4.48
unnamed: R81.1, U4.36
unnamed: R82.2, U4.50
unnamed: R83.2, U4.51
unnamed: R84.2, U4.53
unnamed: R85.1, U4.20
unnamed: R86.1, U4.21
unnamed: R87.1, U4.15
unnamed: R88.1, U4.39
unnamed: R89.1, U4.16
unnamed: R90.1, U4.17
unnamed: R91.1, U4.18
unnamed: R92.1, U4.19
unnamed: R93.1, U4.38
unnamed: R94.1, U4.37
unnamed: R114.2, R116.1, U7.2
unnamed: R115.2, U5.2
unnamed: R117.2, U7.8
unnamed: R118.2, U7.7
unnamed: R119.1, U7.13
unnamed: R120.1, U7.12
unnamed: R121.1, U7.5
unnamed: R122.1, R123.2, U8.3
unnamed: R124.2, R133.1, U10.9
unnamed: R125.2, R130.1, U10.12
unnamed: R126.2, TP7.1
unnamed: R128.2, R131.1, U10.10
unnamed: R129.2, R132.1, U10.7
unnamed: R134.1, U11.5
unnamed: R135.2, R136.2, U11.3
unnamed: R137.2, R139.2, R140.2
unnamed: R174.2, U13.31
unnamed: R175.2, U13.32
unnamed: R184.2, R185.2, U13.174
unnamed: R187.1, SW11.2
unnamed: R206.2, R207.1, U14.4
unnamed: R208.1, R209.2, U14.3
unnamed: R211.2, U15.4
unnamed: R212.2, U15.6
unnamed: R215.2, U16.4
unnamed: R216.2, U16.6
unnamed: R217.2, U7.6
unnamed: TP1.1, U1.30
unnamed: TP2.1, U1.7
unnamed: TP13.1, U13.36
unnamed: TP14.1, U13.10
unnamed: TP15.1, U13.11
VCC_3V3: C1.1, C2.1, C3.1, C50.2, J1.1, J6.1, J7.4, L7.1, R14.2, R95.1, R96.1, R103.1, R104.1, R105.1, R106.1, U1.8, U1.10, U1.32, X1.4
VCC_5V: C4.1, C5.1, C61.1, C62.1, C63.1, J6.2, J6.4, R125.1, R128.1, U1.21, U1.26, U10.13, U10.14, U10.15, U14.5
VCC_BAT: C54.1, C59.1, C67.1, C68.1, C69.1, L10.1, R129.1, U5.3, U6.1, U7.1, U7.20, U8.1, U10.6, U11.1
VCC_BAT+: C21.1, C22.2, C35.1, C70.1, C71.1, L8.1, M2.1, M3.1, R134.2, R137.1, R138.1, U2.10, U2.27, U11.6
VCC_EINK: C40.1, C41.1, J5.5, J5.7, R30.1, R31.1, R36.1, R37.1, R46.1, U2.46
VCC_MCU: C51.1, C52.1, C90.1, C94.1, C102.1, C103.1, C104.1, C105.1, C106.1, C107.1, C108.1, C109.1, C110.1, C111.1, C112.1, C113.1, C114.1, C115.1, C116.1, C117.1, C118.1, C119.1, FB1.1, J11.1, J11.2, R184.1, R186.2, R187.2, R189.1, R190.1, R191.1, R192.1, R201.2, R202.2, R208.2, U6.5, U13.7, U13.8, U13.13, U13.25, U13.44, U13.48, U13.65, U13.71, U13.84, U13.92, U13.99, U13.105, U13.113, U13.120, U13.121, U13.126, U13.136, U13.152, U13.160, U13.176
VCC_PERIH: C42.1, C43.2, C44.2, C45.2, C46.2, C47.2, C48.2, C49.2, C57.1, C58.1, J2.1, J2.2, U2.45, U3.2, U4.1, U4.3, U4.9, U4.14, U4.27, U4.43, U4.49, U8.5
VCC_USB: C121.1, D7.2, D8.2, J13.1, R114.1, R214.2, U7.3, U7.4, U7.9, U7.17, U7.18, U7.19, U16.5
